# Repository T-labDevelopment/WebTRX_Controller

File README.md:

# WebTRX Controller — CH552 USB HID rotary dial (KiCad 10)

Active hardware revision: **Rev.A.2**, with WeAct CH552 Core Board V1.0 module (onboard USB), EC12E2420801 24-detent encoder, and three 12mm tact switches.

The current **editable KiCad schematic + two-layer PCB** and all project-local symbol / footprint libraries are in `hardware/`. Open `hardware/WebTRX_Controller.kicad_pro` in KiCad 10.x. Full hardware instructions and cautions: `hardware/README_JA.md`.

Firmware and HID specification remain unchanged from prior revision: each mechanical click transmits X axis `0 -> +127` / `0 -> -127`, and F1/F2/PTT produce configurable HID key assignments.

**Verification:** Python static connectivity/clearance checks pass, but **KiCad ERC/DRC, actual KiCad project opening, module mechanical fit, switch matching and hardware operation have not been tested.** Not approved for manufacture.

Current work branch: `feature/ch552-module-encoder-12mm-kicad10`; `main` is not updated.

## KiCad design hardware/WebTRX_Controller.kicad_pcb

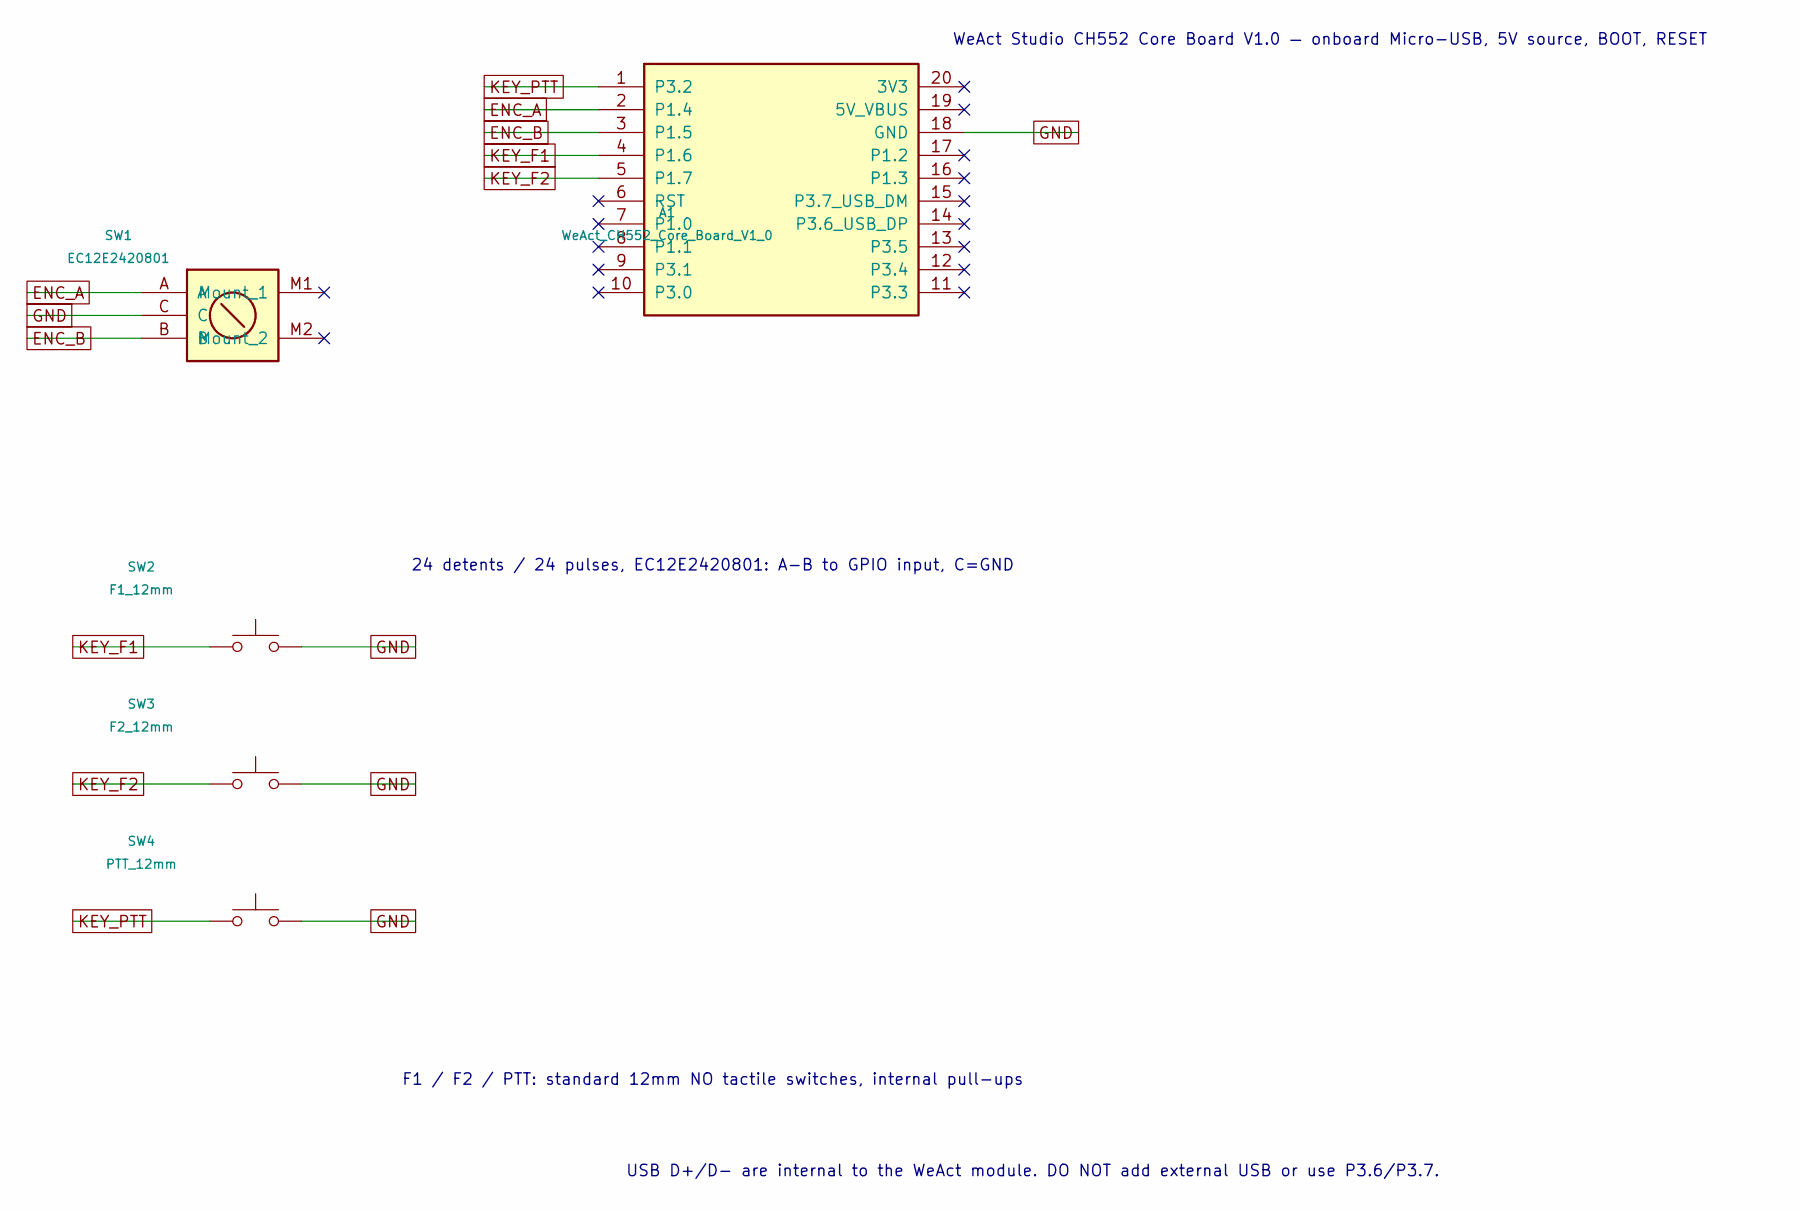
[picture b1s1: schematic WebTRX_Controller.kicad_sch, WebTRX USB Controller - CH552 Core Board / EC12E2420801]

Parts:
A1: WeAct_CH552_Core_Board_V1_0
SW1: EC12E2420801
SW2: F1_12mm; SW_PUSH-12mm
SW3: F2_12mm; SW_PUSH-12mm
SW4: PTT_12mm; SW_PUSH-12mm

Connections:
ENC_A: A1.2 (P1.4), SW1.A
ENC_B: A1.3 (P1.5), SW1.B
GND: A1.18 (GND), SW1.C, SW2.2, SW3.2, SW4.2
KEY_F1: A1.4 (P1.6), SW2.1
KEY_F2: A1.5 (P1.7), SW3.1
KEY_PTT: A1.1 (P3.2), SW4.1

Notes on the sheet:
WeAct Studio CH552 Core Board V1.0 — onboard Micro-USB, 5V source, BOOT, RESET
24 detents / 24 pulses, EC12E2420801: A-B to GPIO input, C=GND
F1 / F2 / PTT: standard 12mm NO tactile switches, internal pull-ups
USB D+/D- are internal to the WeAct module. DO NOT add external USB or use P3.6/P3.7.

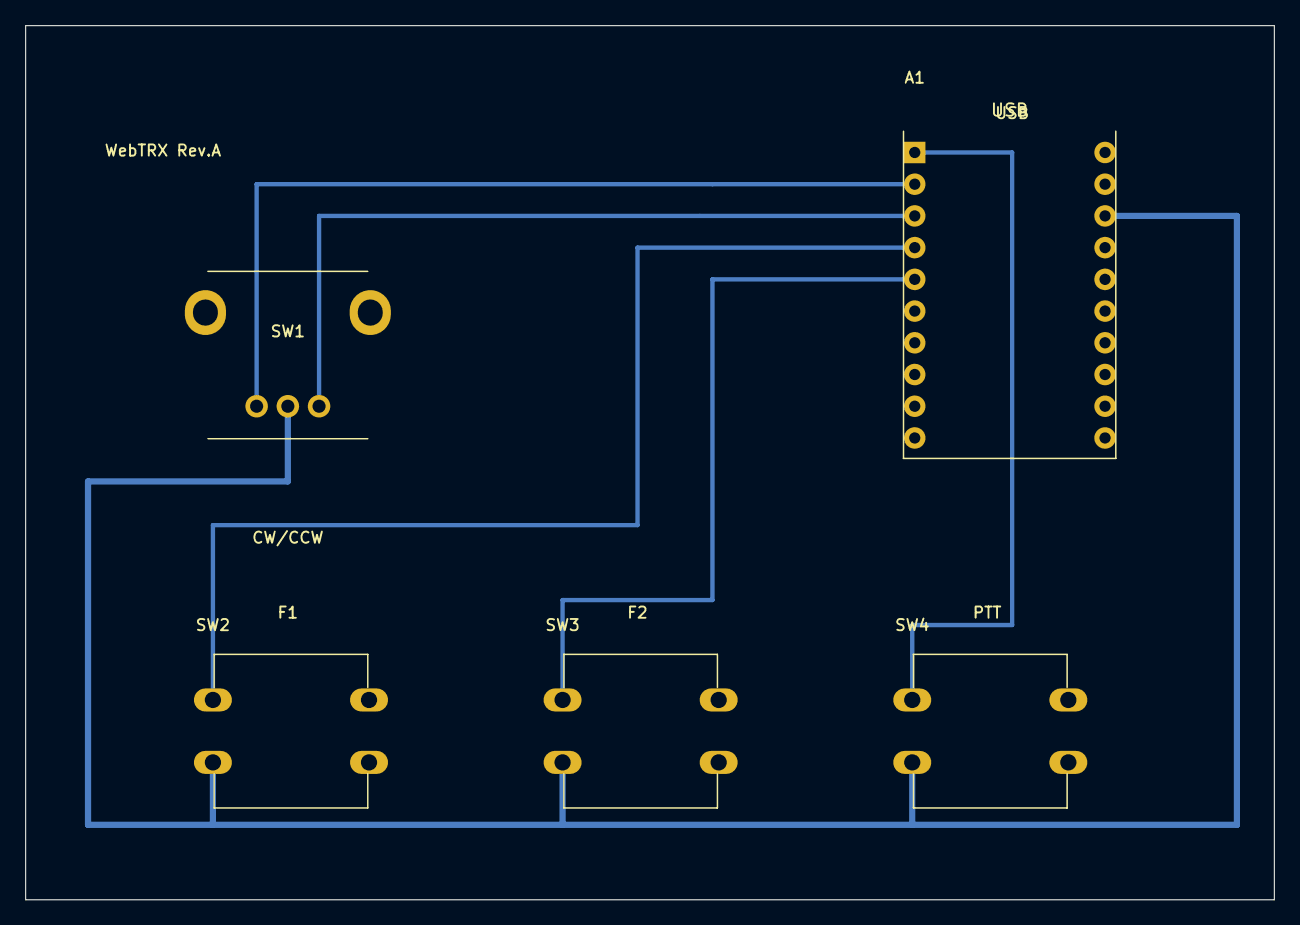
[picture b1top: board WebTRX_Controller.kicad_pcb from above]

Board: 2 copper layers, 100.0 x 70.0 mm, 5 parts (0 on the bottom side), 6 nets.

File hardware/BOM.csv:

Reference,Item,ManufacturerPartNumber,Quantity,UnitPriceJPY,Supply,Footprint,Status
A1,USB MCU board,WeAct Studio CH552 Core Board V1.0 CH552T,1,332,User screenshot,Mounted core board,Selected USB/HID functionality not validated
SW1,Rotary encoder 24 detents / 24 pulses,ALPS Alpine EC12E2420801,1,100,Akizuki g106357,THT 2.5mm pitch,Selected; foot print pin mapping not verified
SW2,Programmable function key F1,NO momentary tactile switch,1,,,To be selected,New
SW3,Programmable function key F2,NO momentary tactile switch,1,,,To be selected,New
SW4,PTT momentary key,NO momentary tactile switch,1,,,To be selected,New safety verification required

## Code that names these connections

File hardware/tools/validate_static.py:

#!/usr/bin/env python3
"""Independent static geometry / net consistency checks (NOT a KiCad ERC/DRC replacement)."""
from pathlib import Path
import re, math, collections, json
P=Path(__file__).resolve().parents[1]
S=(P/'WebTRX_Controller.kicad_sch').read_text(encoding='utf-8')
PCB=(P/'WebTRX_Controller.kicad_pcb').read_text(encoding='utf-8')
LIB=(P/'WebTRX_Custom.kicad_sym').read_text(encoding='utf-8')

def balanced(s):
    depth=0; quoted=False; escaped=False
    for c in s:
        if quoted:
            if escaped:escaped=False
            elif c=='\\':escaped=True
            elif c=='"':quoted=False
        else:
            if c=='"':quoted=True
            elif c=='(':depth+=1
            elif c==')':
                depth-=1
                assert depth>=0,'Extra closing parenthesis'
    assert depth==0 and not quoted,'S-expression balance failed'
for v in [S,PCB,LIB,*[x.read_text() for x in (P/'WebTRX_Custom.pretty').glob('*.kicad_mod')]]:balanced(v)

def splitblocks(s,op):
    out=[]
    for m in re.finditer(re.escape(op),s):
        i=m.start();dep=0;quote=False;escape=False
        for j in range(i,len(s)):
            c=s[j]
            if quote:
                if escape:escape=False
                elif c=='\\':escape=True
                elif c=='"':quote=False
            else:
                if c=='"':quote=True
                elif c=='(':dep+=1
                elif c==')':
                    dep-=1
                    if dep==0:
                        out.append(s[i:j+1]);break
    return out

assert 'WebTRX_Custom:WeAct_CH552_Core_Board_V1_0' in S
assert 'WebTRX_Custom:EC12E2420801' in S
for ref in ['A1','SW1','SW2','SW3','SW4']:assert f'(reference "{ref}")' in S
assert S.count('(no_connect ')==16, S.count('(no_connect ')
labels=[]
for b in splitblocks(S,'(global_label '):
    n=re.search(r'^\(global_label \"([^\"]+)\"',b).group(1)
    x,y,angle=re.search(r'\(at ([-\d.]+) ([-\d.]+) (0|180)\)',b).groups()
    labels.append((n,x,y,angle))
wires=re.findall(r'\(wire \(pts \(xy ([-\d.]+) ([-\d.]+)\) \(xy ([-\d.]+) ([-\d.]+)\)\)',S)
assert len(wires)==len(labels)==15, (len(wires),len(labels))
wired=set()
for a,b,c,d in wires:
    for x,y in [(a,b),(c,d)]:
        assert abs(float(x)/1.27-round(float(x)/1.27))<.00001,('50mil x',x)
        assert abs(float(y)/1.27-round(float(y)/1.27))<.00001,('50mil y',y)
        wired.add((round(float(x),4),round(float(y),4)))
for n,x,y,_ in labels: assert (float(x),float(y)) in wired,('floating label',n,x,y)
assert collections.Counter(n for n,_,_,_ in labels)=={'GND':5,'ENC_A':2,'ENC_B':2,'KEY_F1':2,'KEY_F2':2,'KEY_PTT':2}
# top-level component footprints in PCB
fps=[]
for blk in splitblocks(PCB,'(footprint '):
    ref=re.search(r'\(property "Reference" "([^"]+)"',blk).group(1)
    raw=re.search(r'\(at\s+([\d.]+)\s+([\d.]+)',blk)
    ox,oy=map(float,raw.groups())
    pininfo=[]
    for pad in splitblocks(blk,'(pad '):
        m=re.search(r'^\(pad "([^"]+)" (?:thru_hole|smd) [a-z]+ \(at\s+([-\d.]+)\s+([-\d.]+)',pad)
        if not m:raise AssertionError(('unknown pad syntax',pad[:100]))
        n,x,y=m.groups();x=float(x)+ox;y=float(y)+oy
        net=re.search(r'\(net\s+(\d+)\s+"([^"]+)"\)',pad)
        netname=net.group(2) if net else 'unconnected'
        size=re.search(r'\(size\s+([-\d.]+)\s+([-\d.]+)\)',pad)
        sx,sy=map(float,size.groups())
        pininfo.append((n,x,y,netname,sx,sy))
    fps.append((ref,pininfo))
assert len(fps)==5,[f[0] for f in fps]
padrows=[(ref,*pin) for ref,pins in fps for pin in pins]
assert len(padrows)==20+5+4*3
for ref,pins in fps:
    nums=[p[0] for p in pins]
    if ref=='A1': assert set(nums)==set(map(str,range(1,21)))
    if ref=='SW1':assert set(nums)=={'A','B','C','M1','M2'}
    if ref in {'SW2','SW3','SW4'}:assert collections.Counter(nums)=={'1':2,'2':2}
# TRACK routes on B.Cu must reach at least one pad of each net and avoid crossing unlike nets.
seg=[]
for b in splitblocks(PCB,'(segment '):
    st=re.search(r'\(start\s+([-\d.]+)\s+([-\d.]+)\)',b)
    en=re.search(r'\(end\s+([-\d.]+)\s+([-\d.]+)\)',b)
    w=re.search(r'\(width\s+([-\d.]+)\)',b);n=re.search(r'\(net\s+(\d+)\)',b)
    assert st and en and w and n
    seg.append((tuple(map(float,st.groups())),tuple(map(float,en.groups())),float(w.group(1)),int(n.group(1))))
assert len(seg)==30,len(seg)
NAMES={'GND':1,'ENC_A':2,'ENC_B':3,'KEY_F1':4,'KEY_F2':5,'KEY_PTT':6}
for net,num in NAMES.items():
    endpoints=[p for st,en,w,n in seg if n==num for p in (st,en)]
    assert endpoints,net
    for ref,p,x,y,pnet,sx,sy in padrows:
        if pnet==net:
            # all pads for standard switch have two electrically common pads - at least one must physically reach via copper
            if ref in {'SW2','SW3','SW4'} and x%1!=0:
                continue
            assert any(math.dist(pt,(x,y))<.001 for pt in endpoints),(ref,p,net,(x,y))

def ptseg(P,A,B):
    ax,ay=A;bx,by=B;px,py=P
    l2=(bx-ax)**2+(by-ay)**2
    t=max(0,min(1,((px-ax)*(bx-ax)+(py-ay)*(by-ay))/l2)) if l2 else 0
    return math.dist(P,(ax+t*(bx-ax),ay+t*(by-ay)))
def cross(A,B,C,D):
    def ori(a,b,c):return (b[0]-a[0])*(c[1]-a[1])-(b[1]-a[1])*(c[0]-a[0])
    return ori(A,B,C)*ori(A,B,D)<0 and ori(C,D,A)*ori(C,D,B)<0

def segseg(A,B,C,D):
    if cross(A,B,C,D):return 0
    return min(ptseg(A,C,D),ptseg(B,C,D),ptseg(C,A,B),ptseg(D,A,B))
# DRC-like conservative circle approximation, yet real DRC may differ.
for i,(A,B,w,n) in enumerate(seg):
    for j,(C,D,w2,n2) in enumerate(seg[i+1:],i+1):
        if n==n2:continue
        distance=segseg(A,B,C,D)
        threshold=(w+w2)/2+.22
        assert distance>=threshold-1e-3,('different-net track collision',i,j,distance,threshold)
    for ref,p,x,y,pnet,sx,sy in padrows:
        if pnet!='unconnected' and NAMES.get(pnet)==n:continue
        if pnet=='unconnected' and ref=='A1':
            # Do not route under DIP module unconnected plated pads.
            pass
        # circular worst-case overestimate of oval pad: apply max radius; this is a stronger but incomplete check
        d=ptseg((x,y),A,B)
        threshold=max(sx,sy)/2+w/2+.19
        assert d>=threshold-1e-3,('track to other-net pad',i,ref,p,round(d,4),round(threshold,4),A,B)
# Check module pads and unconnected support metal are fully within PCB edges.
assert all(6<=x<=104 and 1<=y<=69 for ref,p,x,y,n,sx,sy in padrows)
# all pad and segment net IDs matching net table
for n in NAMES:assert f'(net {NAMES[n]} "{n}")' in PCB
assert len(re.findall(r'\(gr_line ',PCB))==4
# project local tables
assert '${KIPRJMOD}/WebTRX_Custom.pretty' in (P/'fp-lib-table').read_text()
assert '${KIPRJMOD}/WebTRX_Custom.kicad_sym' in (P/'sym-lib-table').read_text()
print('PASS: S-expressions, 50mil, logical pins, standalone libraries, PCB pads/tracks, net connectivity and static clearance')
print(f'NOT RUN: KiCad GUI, KiCad CLI/ERC/DRC, USB hardware or assembled fit; {len(seg)} copper segments, {len(padrows)} PCB pads.')
